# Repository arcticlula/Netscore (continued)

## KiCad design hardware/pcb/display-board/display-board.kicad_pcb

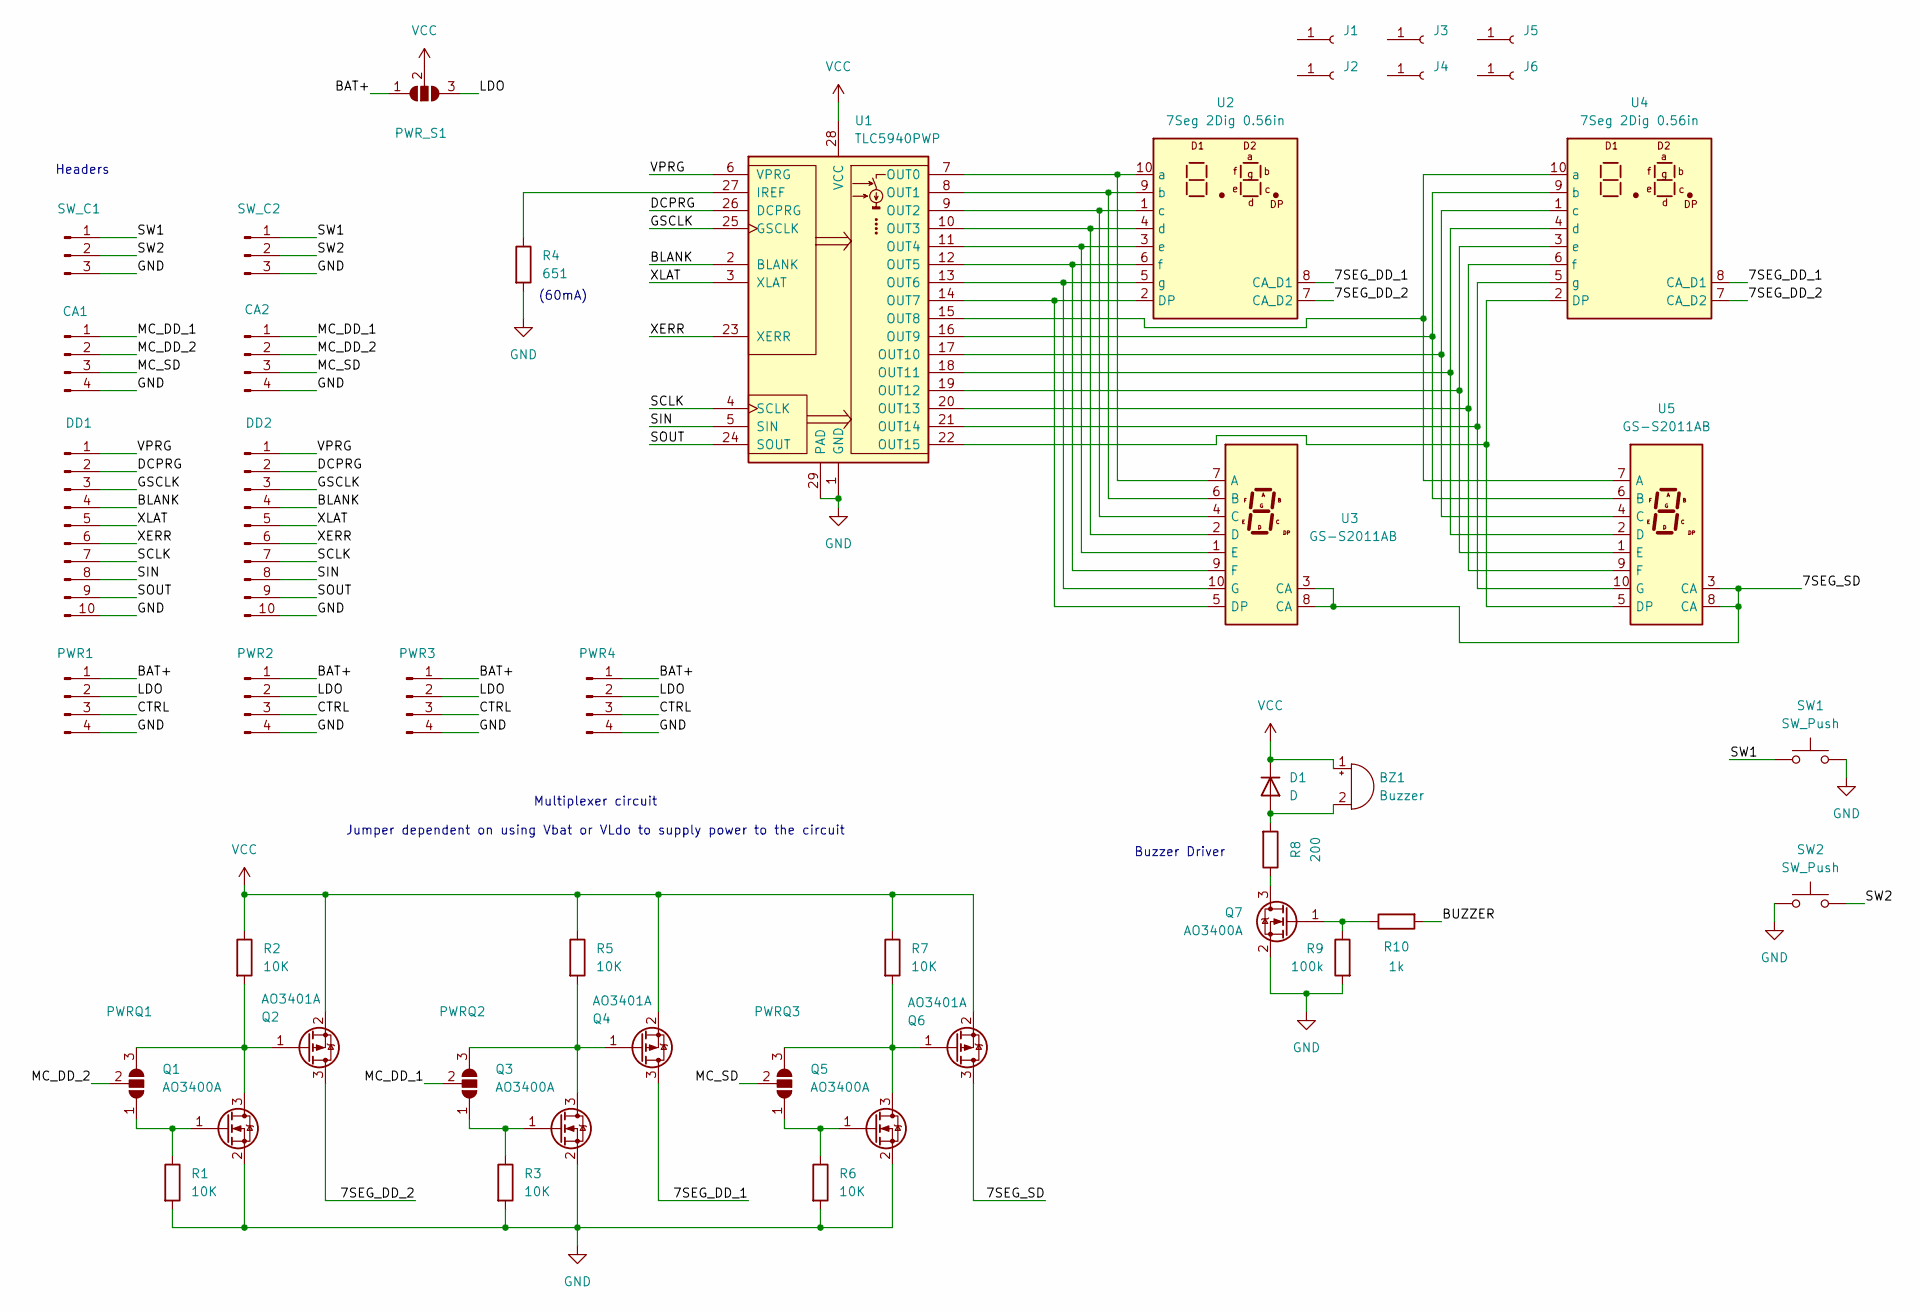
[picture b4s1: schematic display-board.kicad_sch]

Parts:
BZ1: Buzzer; Buzzer_TDK_PS1240P02BT_D12.2mm_H6.5mm
CA1, CA2: Conn_01x04_Pin; PinHeader_1x04_P1.27mm_Vertical
D1: D; D_SOD-323_HandSoldering
DD1, DD2: Conn_01x10_Pin; PinSocket_1x10_P1.27mm_Vertical
J1, J2, J3, J4, J5, J6: Conn_01x01_Socket; MountingHole_2mm
PWR1, PWR2, PWR3, PWR4: Conn_01x04_Pin; PinHeader_1x04_P1.27mm_Vertical
PWRQ1, PWRQ2, PWRQ3: SolderJumper_3_Open; SolderJumper-3_P1.3mm_Open_RoundedPad1.0x1.5mm_NumberLabels
PWR_S1: SolderJumper_3_Open; SolderJumper-3_P1.3mm_Open_RoundedPad1.0x1.5mm_NumberLabels
Q1, Q3, Q5, Q7: AO3400A; SOT-23
Q2, Q4, Q6: AO3401A; SOT-23
R1, R2, R3, R5, R6, R7: 10K; R_0603_1608Metric_Pad0.98x0.95mm_HandSolder
R4: 651; R_0603_1608Metric_Pad0.98x0.95mm_HandSolder
R8: 200; R_0603_1608Metric_Pad0.98x0.95mm_HandSolder
R9: 100k; R_0603_1608Metric_Pad0.98x0.95mm_HandSolder
R10: 1k; R_0603_1608Metric_Pad0.98x0.95mm_HandSolder
SW1, SW2: SW_Push; Button_12x12x7.3
SW_C1, SW_C2: Conn_01x03_Pin; PinHeader_1x03_P1.27mm_Vertical
U1: TLC5940PWP; HTSSOP-28-1EP_4.4x9.7mm_P0.65mm_EP3.4x9.5mm_Mask2.4x6.17mm_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
U2, U4: 7Seg 2Dig 0.56in; 7Seg 0.56In Double
U3, U5: GS-S2011AB; GS-2011AB

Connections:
/7SEG_DD_1: Q4.3 (D), U2.8 (CA_D1), U4.8 (CA_D1)
/7SEG_DD_2: Q2.3 (D), U2.7 (CA_D2), U4.7 (CA_D2)
/7SEG_SD: Q6.3 (D), U3.3 (CA), U3.8 (CA), U5.3 (CA), U5.8 (CA)
/BAT+: PWR1.1, PWR2.1, PWR3.1, PWR4.1, PWR_S1.1 (A); also elsewhere on the board
/BLANK: DD1.4, DD2.4, U1.2 (BLANK)
/BUZZER: R10.2
/CTRL: PWR1.3, PWR2.3, PWR3.3, PWR4.3
/DCPRG: DD1.2, DD2.2, U1.26 (DCPRG)
/GSCLK: DD1.3, DD2.3, U1.25 (GSCLK)
/LDO: PWR1.2, PWR2.2, PWR3.2, PWR4.2, PWR_S1.3 (B); also elsewhere on the board
/MC_DD_1: CA1.1, CA2.1, PWRQ2.2 (C)
/MC_DD_2: CA1.2, CA2.2, PWRQ1.2 (C)
/MC_SD: CA1.3, CA2.3, PWRQ3.2 (C)
/SCLK: DD1.7, DD2.7, U1.4 (SCLK)
/SIN: DD1.8, DD2.8, U1.5 (SIN)
/SOUT: DD1.9, DD2.9, U1.24 (SOUT)
/SW1: SW1.1, SW_C1.1, SW_C2.1
/SW2: SW2.2, SW_C1.2, SW_C2.2
/VPRG: DD1.1, DD2.1, U1.6 (VPRG)
/XERR: DD1.6, DD2.6, U1.23 (XERR)
/XLAT: DD1.5, DD2.5, U1.3 (XLAT)
GND: CA1.4, CA2.4, DD1.10, DD2.10, PWR1.4, PWR2.4, PWR3.4, PWR4.4, Q1.2 (S), Q3.2 (S), Q5.2 (S), Q7.2 (S), R1.2, R3.2, R4.2, R6.2, R9.2, SW1.2, SW2.1, SW_C1.3, SW_C2.3, U1.1 (GND), U1.29 (PAD); also elsewhere on the board
unnamed: BZ1.2 (+), D1.2 (A), R8.2
unnamed: PWRQ1.1 (A), Q1.1 (G), R1.1
unnamed: PWRQ1.3 (B), Q1.3 (D), Q2.1 (G), R2.2
unnamed: PWRQ2.1 (A), Q3.1 (G), R3.1
unnamed: PWRQ2.3 (B), Q3.3 (D), Q4.1 (G), R5.2
unnamed: PWRQ3.1 (A), Q5.1 (G), R6.1
unnamed: PWRQ3.3 (B), Q5.3 (D), Q6.1 (G), R7.2
unnamed: Q7.3 (D), R8.1
unnamed: Q7.1 (G), R9.1, R10.1
unnamed: R4.1, U1.27 (IREF)
unnamed: U1.7 (OUT0), U2.10 (a), U3.7 (A)
unnamed: U1.8 (OUT1), U2.9 (b), U3.6 (B)
unnamed: U1.9 (OUT2), U2.1 (c), U3.4 (C)
unnamed: U1.10 (OUT3), U2.4 (d), U3.2 (D)
unnamed: U1.11 (OUT4), U2.3 (e), U3.1 (E)
unnamed: U1.12 (OUT5), U2.6 (f), U3.9 (F)
unnamed: U1.13 (OUT6), U2.5 (g), U3.10 (G)
unnamed: U1.14 (OUT7), U2.2 (DP), U3.5 (DP)
unnamed: U1.15 (OUT8), U4.10 (a), U5.7 (A)
unnamed: U1.16 (OUT9), U4.9 (b), U5.6 (B)
unnamed: U1.17 (OUT10), U4.1 (c), U5.4 (C)
unnamed: U1.18 (OUT11), U4.4 (d), U5.2 (D)
unnamed: U1.19 (OUT12), U4.3 (e), U5.1 (E)
unnamed: U1.20 (OUT13), U4.6 (f), U5.9 (F)
unnamed: U1.21 (OUT14), U4.5 (g), U5.10 (G)
unnamed: U1.22 (OUT15), U4.2 (DP), U5.5 (DP)
VCC: BZ1.1 (-), D1.1 (K), PWR_S1.2 (C), Q2.2 (S), Q4.2 (S), Q6.2 (S), R2.1, R5.1, R7.1, U1.28 (VCC)

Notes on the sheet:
Headers
(60mA)
Buzzer Driver
Multiplexer circuit Jumper dependent on using Vbat or VLdo to supply power to the circuit

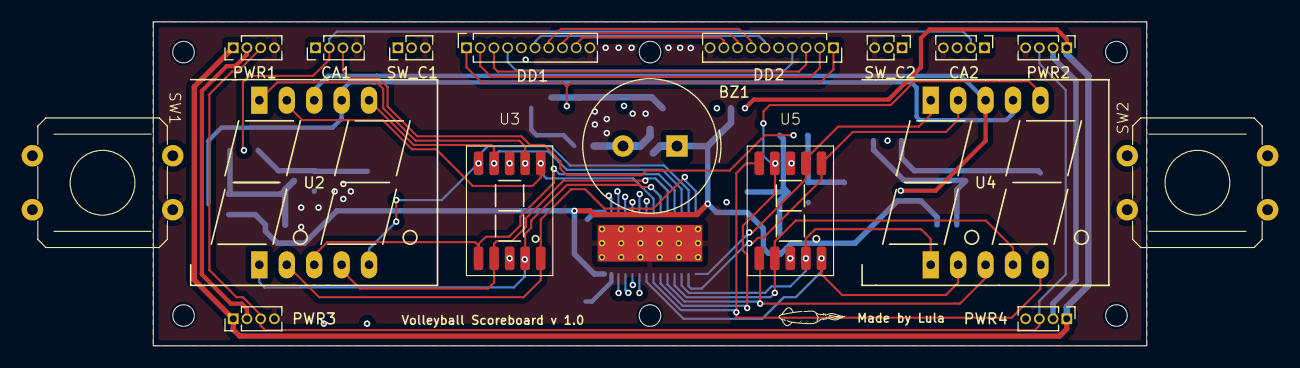
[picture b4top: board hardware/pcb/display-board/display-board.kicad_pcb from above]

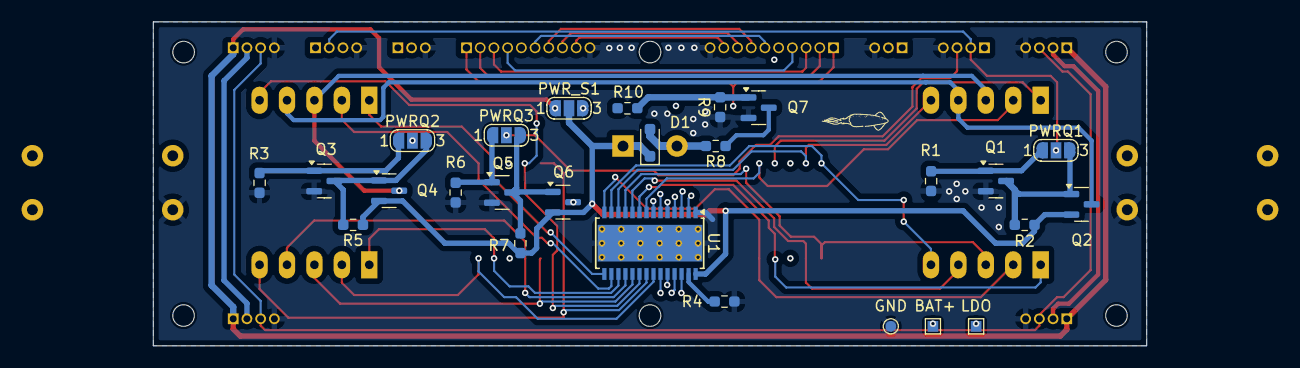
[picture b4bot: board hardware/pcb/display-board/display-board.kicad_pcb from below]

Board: 4 copper layers, 92.0 x 30.0 mm, 49 parts (26 on the bottom side), 48 nets.

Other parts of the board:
BAT+: TestPoint_Pad_1.0x1.0mm
GND: TestPoint_Pad_D1.0mm
LDO: TestPoint_Pad_1.0x1.0mm

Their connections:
/BAT+: BAT+.1; also elsewhere on the board
/LDO: LDO.1; also elsewhere on the board
GND: GND.1; also elsewhere on the board

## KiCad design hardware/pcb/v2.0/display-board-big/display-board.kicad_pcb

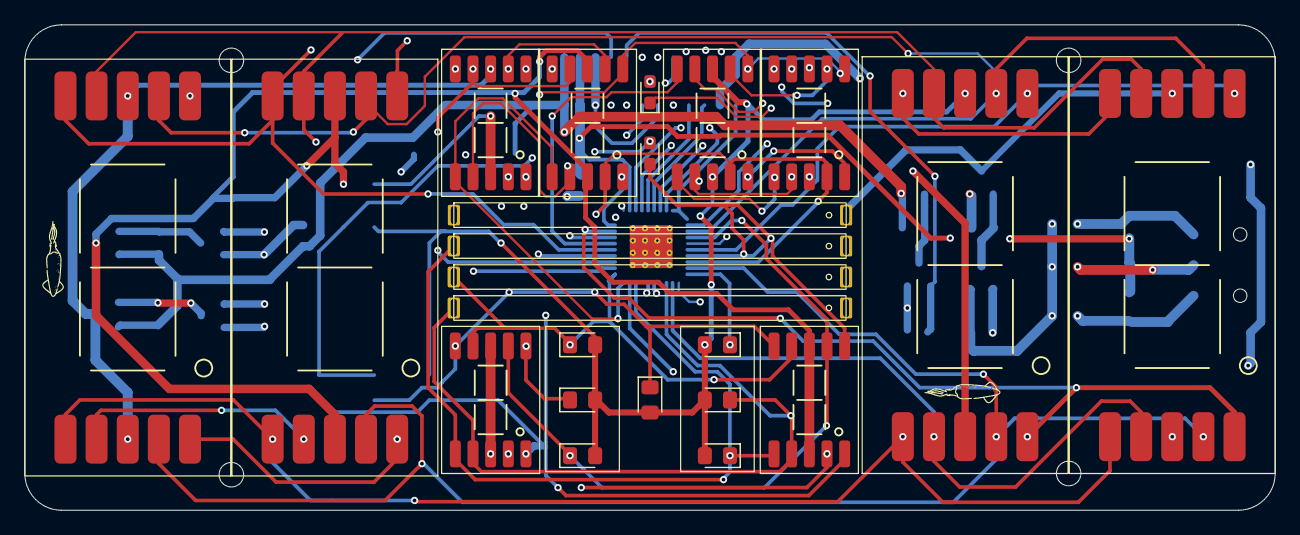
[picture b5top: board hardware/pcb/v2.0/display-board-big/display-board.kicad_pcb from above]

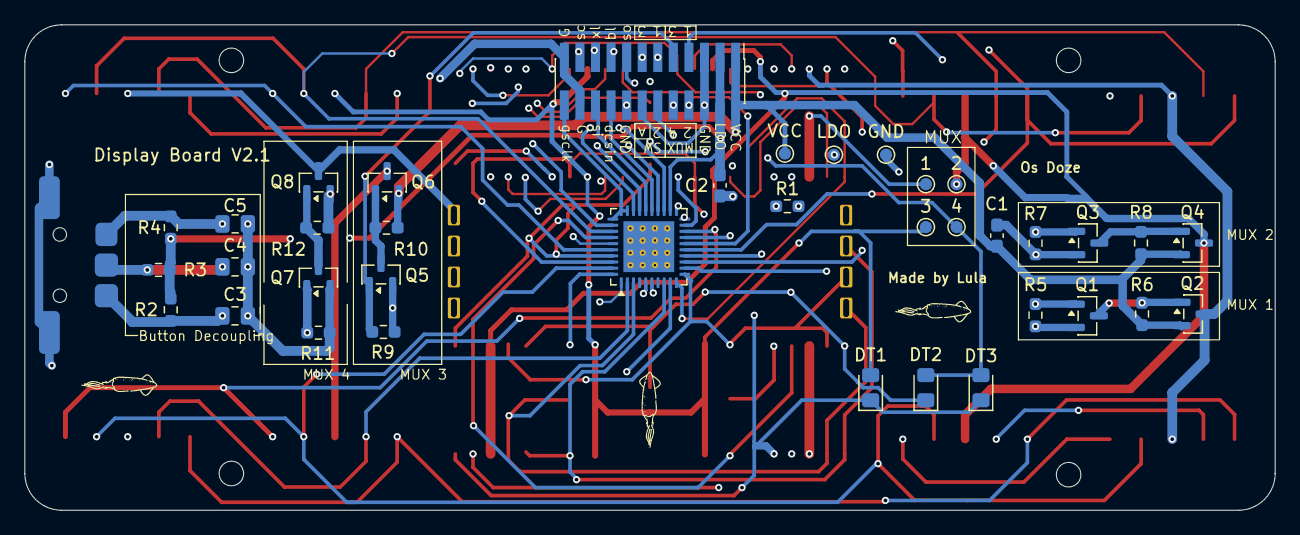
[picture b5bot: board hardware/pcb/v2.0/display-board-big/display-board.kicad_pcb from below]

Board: 4 copper layers, 102.0 x 39.6 mm, 65 parts (38 on the bottom side), 51 nets.

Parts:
1, 2, 3, 4: TestPoint; TestPoint_Pad_D1.0mm
A1: Conn_02x12_Odd_Even; PinHeader_2x12_P1.27mm_Vertical_SMD
C1: 10uF; C_0603_1608Metric_Pad1.08x0.95mm_HandSolder
C2: 0.1uF; C_0603_1608Metric_Pad1.08x0.95mm_HandSolder
C3, C4, C5: 2.2uF; C_0805_2012Metric_Pad1.18x1.45mm_HandSolder
D1, D6, D13, D14: BAR LED; LED Bar
D3, D4, D5, D7, D8, D9, D10: LED; LED_0805_2012Metric_Pad1.15x1.40mm_HandSolder
D11, D12: LED; LED_0603_1608Metric_Pad1.05x0.95mm_HandSolder
DT1, DT2, DT3: LED; LED_0805_2012Metric_Pad1.15x1.40mm_HandSolder
GND: TestPoint; TestPoint_Pad_D1.0mm
H1, H2, H3, H4: MountingHole; MountingHole_2mm
LDO: TestPoint; TestPoint_Pad_D1.0mm
Q1, Q3, Q5, Q7: AO3400A; SOT-23
Q2, Q4, Q6, Q8: AO3401A; SOT-23
R1: 651; R_0603_1608Metric_Pad0.98x0.95mm_HandSolder
R2, R3, R4: 100k; R_0603_1608Metric_Pad0.98x0.95mm_HandSolder
R5, R6, R7, R8, R9, R10, R11, R12: 10K; R_0603_1608Metric_Pad0.98x0.95mm_HandSolder
SW1: Thumbwheel
U1: TLC5951RHA; Texas_RHA0040B_VQFN-40-1EP_6x6mm_P0.5mm_EP4.15x4.15mm_Therm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
U2, U4, U9, U11: SMD 0.8in; 7Seg SMD 0.8in Single
U3, U5, U6, U7, U8, U10: GS-S2011AB; GS-2011AB
VCC: TestPoint; TestPoint_Pad_D1.0mm

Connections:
/7SEG_MUX_1: 1.1, Q2.3 (D), U2.3 (CA), U2.8 (CA), U3.3 (CA), U3.8 (CA), U6.3 (CA), U6.8 (CA)
/7SEG_MUX_2: 2.1, Q4.3 (D), U4.3 (CA), U4.8 (CA), U5.3 (CA), U5.8 (CA), U7.3 (CA), U7.8 (CA)
/7SEG_MUX_3: 3.1, D3.2 (A), D4.2 (A), D5.2 (A), D7.2 (A), D8.2 (A), D9.2 (A), D10.2 (A), DT1.2 (A), Q6.3 (D), U8.3 (CA), U8.8 (CA), U9.3 (CA), U9.8 (CA)
/7SEG_MUX_4: 4.1, D1.2 (A), D6.2 (A), D11.2 (A), D12.2 (A), D13.2 (A), D14.2 (A), DT2.2 (A), DT3.2 (A), Q8.3 (D), U10.3 (CA), U10.8 (CA), U11.3 (CA), U11.8 (CA)
/BLANK: A1.17, U1.23 (XBLNK)
/DCSIN: A1.18, U1.25 (DCSIN)
/DCSOUT: A1.16, U1.6 (DCSOUT)
/GSCLK: A1.24, U1.29 (GSCKG), U1.30 (GSCKR), U1.31 (GSCKB)
/GSLAT: A1.19, U1.28 (GSLAT)
/GSSIN: A1.20, U1.26 (GSSIN)
/GSSOUT: A1.15, U1.5 (GSSOUT)
/LDO_CTRL: A1.3, A1.4, C2.1, LDO.1, R2.1, R3.1, R4.1, U1.22 (VCC)
/MUX_1: A1.7, Q1.1 (G), R5.1
/MUX_2: A1.8, Q3.1 (G), R7.1
/MUX_3: A1.9, Q5.1 (G), R9.1
/MUX_4: A1.10, Q7.1 (G), R11.1
/OUTB0: D5.1 (K), D11.1 (K), U1.34 (OUTB0), U6.7 (A), U7.7 (A)
/OUTB1: D4.1 (K), D12.1 (K), U1.37 (OUTB1), U6.6 (B), U7.6 (B)
/OUTB2: D1.1 (K), D8.1 (K), U1.40 (OUTB2), U6.4 (C), U7.4 (C)
/OUTB3: D6.1 (K), D9.1 (K), U1.3 (OUTB3), U6.2 (D), U7.2 (D)
/OUTB4: D10.1 (K), D13.1 (K), U1.8 (OUTB4), U6.1 (E), U7.1 (E)
/OUTB5: D3.1 (K), D14.1 (K), U1.11 (OUTB5), U6.9 (F), U7.9 (F)
/OUTB6: D7.1 (K), DT2.1 (K), U1.14 (OUTB6), U6.10 (G), U7.10 (G)
/OUTB7: DT1.1 (K), DT3.1 (K), U1.17 (OUTB7), U6.5 (DP), U7.5 (DP)
/OUTG0: U1.32 (OUTG0), U3.7 (A), U5.7 (A), U8.7 (A), U10.7 (A)
/OUTG1: U1.35 (OUTG1), U3.6 (B), U5.6 (B), U8.6 (B), U10.6 (B)
/OUTG2: U1.38 (OUTG2), U3.4 (C), U5.4 (C), U8.4 (C), U10.4 (C)
/OUTG3: U1.1 (OUTG3), U3.2 (D), U5.2 (D), U8.2 (D), U10.2 (D)
/OUTG4: U1.10 (OUTG4), U3.1 (E), U5.1 (E), U8.1 (E), U10.1 (E)
/OUTG5: U1.13 (OUTG5), U3.9 (F), U5.9 (F), U8.9 (F), U10.9 (F)
/OUTG6: U1.16 (OUTG6), U3.10 (G), U5.10 (G), U8.10 (G), U10.10 (G)
/OUTG7: U1.19 (OUTG7), U3.5 (DP), U5.5 (DP), U8.5 (DP), U10.5 (DP)
/OUTR0: U1.33 (OUTR0), U2.7 (A), U4.7 (A), U9.7 (A), U11.7 (A)
/OUTR1: U1.36 (OUTR1), U2.6 (B), U4.6 (B), U9.6 (B), U11.6 (B)
/OUTR2: U1.39 (OUTR2), U2.4 (C), U4.4 (C), U9.4 (C), U11.4 (C)
/OUTR3: U1.2 (OUTR3), U2.2 (D), U4.2 (D), U9.2 (D), U11.2 (D)
/OUTR4: U1.9 (OUTR4), U2.1 (E), U4.1 (E), U9.1 (E), U11.1 (E)
/OUTR5: U1.12 (OUTR5), U2.9 (F), U4.9 (F), U9.9 (F), U11.9 (F)
/OUTR6: U1.15 (OUTR6), U2.10 (G), U4.10 (G), U9.10 (G), U11.10 (G)
/OUTR7: U1.18 (OUTR7), U2.5 (DP), U4.5 (DP), U9.5 (DP), U11.5 (DP)
/SCLK: A1.21, U1.24 (DCSCK), U1.27 (GSSCK)
/SW_1: A1.11, C3.1, R2.2, SW1.1
/SW_2: A1.12, C4.1, R3.2, SW1.T
/SW_3: A1.13, C5.1, R4.2, SW1.2
/VCC_CTRL: A1.1, A1.2, C1.1, Q2.2 (S), Q4.2 (S), Q6.2 (S), Q8.2 (S), R6.1, R8.1, R10.1, R12.1, VCC.1
GND: A1.5, A1.6, A1.14, A1.22, A1.23, C1.2, C2.2, C3.2, C4.2, C5.2, GND.1, Q1.2 (S), Q3.2 (S), Q5.2 (S), Q7.2 (S), R1.2, R5.2, R7.2, R9.2, R11.2, SW1.C, U1.20 (GND), U1.41 (GND)
unnamed: Q1.3 (D), Q2.1 (G), R6.2
unnamed: Q3.3 (D), Q4.1 (G), R8.2
unnamed: Q5.3 (D), Q6.1 (G), R10.2
unnamed: Q7.3 (D), Q8.1 (G), R12.2
unnamed: R1.1, U1.21 (IREF)

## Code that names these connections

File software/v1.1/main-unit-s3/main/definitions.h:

#pragma once
#include <stdint.h>

#define DEBUG_BAT

#define ENABLE_BUZZER 1

#ifndef LOW
#define LOW 0
#endif

#ifndef HIGH
#define HIGH 1
#endif

#define MAX_BRIGHT 63
#define BRIGHT_INDEX 2
#define MAX_BRIGHT_INDEX 6

#define MAX_VALUE 4095
#define MUX_NUM 3
#define BAT_MIN_LEVEL 3000
#define BAT_MAX_LEVEL 4200

#define MIN_SCORE_VOLLEY 15
#define MAX_SCORE_VOLLEY 25

#define MIN_SCORE_PING_PONG 11
#define MAX_SCORE_PING_PONG 21

#define MAX_SETS 15

#define BIG_RED 90
#define BIG_PURE_GREEN 50
#define SMALL_RED 90
#define SMALL_GREEN 100

#define SMALL_HOLD_TIME_MS 500
#define BIG_HOLD_TIME_MS 1200

#define ADC_VREF_PIN 1
#define ADC_VREF_EN_PIN 3

#define ADC_BAT_PIN ADC_CHANNEL_1
#define ADC_BAT_EN_PIN 4

// #define BUTTON_LEFT_PIN   5
// #define BUTTON_RIGHT_PIN  4
#define BUTTON_LEFT_PIN 5
#define BUTTON_RIGHT_PIN 6
#define VCC_CTRL_EN 14
// #define LDO_CTRL_EN  4
#define LDO_LATCH 45
#define LED_PIN 15
// #define BUZZER_PIN   6
#define BUZZER_A_PIN 42
#define BUZZER_B_PIN 7
#define BUZZER_A_LEDC_CHN LEDC_CHANNEL_2
#define BUZZER_B_LEDC_CHN LEDC_CHANNEL_3

#define DEFAULT_TLC_MOSI_PIN 35
#define DEFAULT_TLC_MISO_PIN 37
#define DEFAULT_TLC_SCK_PIN 36
// #define DEFAULT_XLAT_PIN     33
#define DEFAULT_XLAT_PIN 17
#define DEFAULT_BLANK_PIN 16
#define DEFAULT_GSCLK_PIN 18
// #define DEFAULT_VPRG_PIN    40
#define DEFAULT_VPRG_PIN 21
// #define DEFAULT_DCPRG_PIN    39
#define DEFAULT_DCPRG_PIN 38
#define DEFAULT_XERR_PIN -1

#define MUX_A_DD_1 41
#define MUX_A_DD_2 40
#define MUX_A_SD 39

#define MUX_B_DD_1 8
#define MUX_B_DD_2 9
#define MUX_B_SD 10

typedef void (*timer_callback_t)(void *arg);
typedef void (*callback_t)();

typedef enum {
  BOOT_SCR = 0,
  BOOT_2_SCR,
  BOOT_3_SCR,
  BOOT_4_SCR,
  // PRESS_SCR,
  SPORT_SCR,
  MENU_SCR,
  MENU_TRANSITION_SCR,
  SET_MAX_SCORE_SCR,
  SET_PADEL_GAME_TYPE_SCR,
  SET_PADEL_DEUCE_TYPE_SCR,
  PLAY_SCR,
  PLAY_HOME_WIN_SCR,
  PLAY_AWAY_WIN_SCR,
  BRILHO_SCR,
  BATT_SCR,
  BATT_DEVICE_SCR,
  TEST_SCR,
  OFF_SCR,
  OFF_2_SCR,
} screen_t;

typedef enum {
  SPORT_VOLLEY = 0,
  SPORT_PING_PONG,
  SPORT_PADEL
} sport_menu_options_t;

typedef enum {
  MENU_PLAY = 0,
  MENU_BRILHO,
  MENU_BATT,
  MENU_TEST,
  MENU_OFF
} menu_options_t;

typedef enum {
  SIDE_A = 0,
  SIDE_B,
  SIDE_BOTH,
  SIDE_NONE
} side_t;

typedef enum {
  BEGIN,
  ADD_POINT,
  UNDO_POINT
} action_t;

typedef enum {
  HOME = 0,
  AWAY,
  LAST_TEAM
} team_t;

enum {
  HOME_WIN = 0,
  AWAY_WIN,
  UNDO
};

enum {
  FIRST = 0,
  LAST
};

enum {
  TOURNAMENT = 0,
  TIEBREAK
};

enum {
  GOLDEN_POINT = 0,
  ADVANTAGES
};

// Last action timestamp
extern uint32_t last_action;

// Current screen
extern int8_t window;
// Current sport
extern int8_t sport;
// Selected options
extern int8_t menu;

// Screen brightness vector
extern uint8_t brightness[6];
extern uint8_t brightness_index;
extern uint8_t brightness_animated_index;

typedef struct {
  uint8_t first[2];
  uint8_t last[2];
  uint8_t current;
} option_string_2_t;

extern uint8_t menu_options[5][6];

extern option_string_2_t padel_game_type_option;
extern option_string_2_t padel_deuce_option;

// Segment Configuration
#define SEGMENT_CONFIG_1 1
#define SEGMENT_CONFIG_2 2

#define ACTIVE_SEGMENT_CONFIG SEGMENT_CONFIG_2

#if ACTIVE_SEGMENT_CONFIG == SEGMENT_CONFIG_1
// Red with small green, Green with small red
#define SEGMENT_A_VALUES {BIG_RED, BIG_RED, SMALL_GREEN, SMALL_GREEN, BIG_RED, BIG_RED}
#define SEGMENT_B_VALUES {BIG_PURE_GREEN, BIG_PURE_GREEN, SMALL_RED, SMALL_RED, BIG_PURE_GREEN, BIG_PURE_GREEN}
#elif ACTIVE_SEGMENT_CONFIG == SEGMENT_CONFIG_2
// Red split with Green, Green split with Red
#define SEGMENT_A_VALUES {BIG_RED, BIG_RED, SMALL_RED, SMALL_GREEN, BIG_PURE_GREEN, BIG_PURE_GREEN}
#define SEGMENT_B_VALUES {BIG_PURE_GREEN, BIG_PURE_GREEN, SMALL_GREEN, SMALL_RED, BIG_RED, BIG_RED}
#endif

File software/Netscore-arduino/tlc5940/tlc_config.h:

/*  Copyright (c) 2009 by Alex Leone <acleone ~AT~ gmail.com>

    This file is part of the Arduino TLC5940 Library.

    The Arduino TLC5940 Library is free software: you can redistribute it
    and/or modify it under the terms of the GNU General Public License as
    published by the Free Software Foundation, either version 3 of the
    License, or (at your option) any later version.

    The Arduino TLC5940 Library is distributed in the hope that it will be
    useful, but WITHOUT ANY WARRANTY; without even the implied warranty of
    MERCHANTABILITY or FITNESS FOR A PARTICULAR PURPOSE.  See the
    GNU General Public License for more details.

    You should have received a copy of the GNU General Public License
    along with The Arduino TLC5940 Library.  If not, see
    <http://www.gnu.org/licenses/>. */

#ifndef TLC_CONFIG_H
#define TLC_CONFIG_H

#include <stdint.h>

/** \file
    Configuration for the Arduino Tlc5940 library.  After making changes to
    this file, delete Tlc5940.o in this folder so the changes are applied.

    A summary of all the options:
    - Number of TLCs daisy-chained: NUM_TLCS (default 1)
    - Enable/Disable VPRG functionality: VPRG_ENABLED (default 0)
    - Enable/Disable XERR functionality: XERR_ENABLED (default 0)
    - Should the library use bit-banging (any pins) or hardware SPI (faster):
        DATA_TRANSFER_MODE (default TLC_SPI)
    - Which pins to use for bit-banging: SIN_PIN, SIN_PORT, SIN_DDR and
        SCLK_PIN, SCLK_PORT, SCLK_DDR
    - The PWM period: TLC_PWM_PERIOD (be sure to change TLC_GSCLK_PERIOD
        accordingly!)

    How to change the pin mapping:
    - Arduino digital pin 0-7  = PORTD, PD0-7
    - Arduino digital pin 8-13 = PORTB, PB0-5
    - Arduino analog pin  0-5  = PORTC, PC0-5 */

/** Bit-bang using any two i/o pins */
#define TLC_BITBANG        1
/** Use the much faster hardware SPI module */
#define TLC_SPI            2

/* ------------------------ START EDITING HERE ----------------------------- */

/** Number of TLCs daisy-chained.  To daisy-chain, attach the SOUT (TLC pin 17)
    of the first TLC to the SIN (TLC pin 26) of the next.  The rest of the pins
    are attached normally.
    \note Each TLC needs it's own IREF resistor */
#ifndef NUM_TLCS
#define NUM_TLCS    2
#endif

/** Determines how data should be transfered to the TLCs.  Bit-banging can use
    any two i/o pins, but the hardware SPI is faster.
    - Bit-Bang = TLC_BITBANG
    - Hardware SPI = TLC_SPI (default) */
#define DATA_TRANSFER_MODE    TLC_SPI

/* This include is down here because the files it includes needs the data
   transfer mode */
#include "Espressif_ESP32.h"
#include <SPI.h>


/** If more than 16 TLCs are daisy-chained, the channel type has to be uint16_t.
    Default is uint8_t, which supports up to 16 TLCs. */
#define TLC_CHANNEL_TYPE    uint8_t

/** Determines how long each PWM period should be, in clocks.
    \f$\displaystyle f_{PWM} = \frac{f_{osc}}{2 * TLC\_PWM\_PERIOD} Hz \f$
    \f$\displaystyle TLC\_PWM\_PERIOD = \frac{f_{osc}}{2 * f_{PWM}} \f$
    This is related to TLC_GSCLK_PERIOD:
    \f$\displaystyle TLC\_PWM\_PERIOD =
       \frac{(TLC\_GSCLK\_PERIOD + 1) * 4096}{2} \f$
    \note The default of 8192 means the PWM frequency is 976.5625Hz */
#define TLC_PWM_PERIOD    8192

/** Determines how long each period GSCLK is.
    This is related to TLC_PWM_PERIOD:
    \f$\displaystyle TLC\_GSCLK\_PERIOD =
       \frac{2 * TLC\_PWM\_PERIOD}{4096} - 1 \f$
    \note Default is 3 */
#define TLC_GSCLK_PERIOD    3

/** Enables/disables VPRG (TLC pin 27) functionality.  If you need to set dot
    correction data, this needs to be enabled.
    - 0 VPRG is not connected.  <em>TLC pin 27 must be grounded!</em> (default)
    - 1 VPRG is connected
    \note VPRG to GND inputs grayscale data, VPRG to Vcc inputs dot-correction
          data */
#define VPRG_ENABLED    1

/** Enables/disables XERR (TLC pin 16) functionality to check for shorted/broken
    LEDs
    - 0 XERR is not connected (default)
    - 1 XERR is connected
    \note XERR is active low */
#define XERR_ENABLED    0

// Enable/disable test board
#define TEST_BOARD    0

/* ------------------------- STOP EDITING HERE ----------------------------- */


#if !(DATA_TRANSFER_MODE == TLC_BITBANG \
 || DATA_TRANSFER_MODE == TLC_SPI)
#error "Invalid DATA_TRANSFER_MODE specified, see DATA_TRANSFER_MODE"
#endif

/* Various Macros */

/** Arranges 2 grayscale values (0 - 4095) in the packed array format (3 bytes).
    This is for array initializers only: the output is three comma seperated
    8-bit values. */
//#define GS_DUO(a, b)  ((a) >> 4), ((a) << 4) | ((b) >> 8), (b)
#define GS_DUO(a, b)    (uint8_t)((a) >> 4), (uint8_t)((a) << 4) | (uint8_t)((b) >> 8), (uint8_t)(b)


#if VPRG_ENABLED
/** Arranges 4 dot correction values (0 - 63) in the packed array format.
    \see setDCtoProgmemArray */
#define DC_QUARTET(a, b, c, d)   ((a) << 2) | ((b) >> 4), \
                                 ((b) << 4) | ((c) >> 2), \
                                 ((c) << 6) | (d)
#endif

#endif

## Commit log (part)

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2024-11-04 Added display board pcb
2025-01-12 Added main board to the hw folder, some 3d models for the inner structure and the code itself
2025-03-03 Added project basis, software, hardware and 3d models
2025-03-11 renamed some funcs/vars from camelCase to snake_case, added padel, moved initTasks to the end
2025-03-11 improved system (tasks) stability, completed padel mode with new set_win and set_score screens
2025-03-12 added menu_transition, fixed off screen
2025-11-27 button logic is done now in the hub to reduce latency between click and release, restructured folders
2025-11-27 more than one button can be paired and connection status
2025-12-17 Remove .vscode from git and add to .gitignore
2025-12-17 Changed stack to use ble instead (hid over gatt), added new type of button (ITAG) and support for different Ab Shutter models (1 and 2 buttons))
2025-12-18 redid the button logic so the main focus is each different screen, and then the different button presses; undo point reverts for each team instead of previous, reworked the flow
2025-12-22 some cleanup and formatting
2025-12-22 added sdkconfig
2025-12-28 refined screens, redid the point history logic, created a web version for easier development
2026-03-03 moved web display
2026-03-03 added relevant docs
2026-03-03 added improved versions for the struct
    bottom has now the ability to attach suction cups (padel glass)
    inner struct has been simplified to be printable in one go
2026-03-03 improved bl connection logic, refractored led value weight and its now being applied to the correct digits
    added nvs storage also
2026-03-03 created a version of the original esp32/esp32s2 code to run on an esp32s3
2026-03-03 Created new version where it is all centralized in the esp32s3
    also created side unit, can act as a receiver for the main unit and mirror its content
2026-03-04 Fixed ble and wifi transmission issues
    in part because of a hardware antenna replacement
2026-03-09 updated v2 main board
    removed redundant parts (light sensor that was never used and many jumpers)
    added an analog switch to detect and route mosi signal to display board
    fixed batt circuit
    replaced single row connectors by one double each side (mirrored)
2026-03-11 updated main board schematic
2026-03-11 changed display logic to not be tied down to the 2ms alarm that sends data to the tcl5940
2026-03-16 added docs and v2 of the main pcb is about done
2026-03-19 v2.0 of the main and display board is ready and in production
2026-03-19 Added more docs
2026-04-15 detected wrong connections in the rtc module
2026-04-30 new version in the works, time is not yet functional but the new board is very much working
    ds3231 vbat is switched with the vcc - fixed
    have to fix capacitor resonance since it is really annoying
2026-05-18 refined screens in v2.0, usb detection and sleep modes, some tweaks in the spi transmission solves brightness switching, esp now disabled for now since the peak currents sometimes reset the led driver
    also matched the netscore online demo's logic to the currently being used on the devices, developed new 3d models for the new boards
2026-05-19 testing big board
2026-06-29 Added new web simulator for new board revision with time digits, added web app to control settings and retrieve match data, regarding the unit see description
    added more sports
    added mirror mode (in progress still)
    added config menu to play screen
    serve select mode
    some test modes (all is good to check if everything lights up)
    added boot to match shortcuts
